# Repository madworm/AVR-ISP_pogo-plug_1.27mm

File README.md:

AVR-ISP_pogo-plug_1.27mm
========================

LAYOUT FILES: AVR-ISP adapter: 6pin (2.54mm) --> 6pin pogo-pins (1.27mm). 

When your boards get smaller and smaller and it gets harder and harder
to find a spot for the programming connector.

Pogo-pin type: "P50 - E2", 0.68mm body diameter, 0.9mm head diameter.

PCB thickness: 0.6mm !

---

Before having PC-boards made, please make sure you know about your manufacturer's peculiarities!
Especially drill-sizes and their tolerances may vary too much and give you trouble.

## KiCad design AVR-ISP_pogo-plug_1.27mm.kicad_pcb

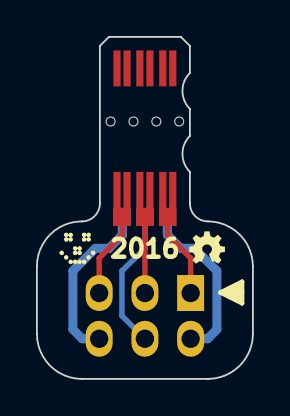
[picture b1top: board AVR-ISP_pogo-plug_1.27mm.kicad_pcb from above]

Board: 2 copper layers, 12.0 x 19.0 mm, 4 parts (0 on the bottom side), 6 nets.

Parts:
G1: LED_smile_silkscreen_2mm
G2: OSHW-logo_silkscreen_2mm
P1: CONN_6; MADW__PIN_ARRAY_3x2_2.54mm
P2: CONN_6; MADW__PIN_ARRAY_3x2_1.27mm

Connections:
/GND: P1.6, P2.6
/MISO: P1.1, P2.1
/MOSI: P1.4, P2.4
/RESET: P1.5, P2.5
/SCK: P1.3, P2.3
/V-target: P1.2, P2.2

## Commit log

2013-05-25 Initial commit.
2013-05-27 Updated 'README.md'.
2013-06-09 Added 2 break-away sub-boards supposed to act as pogo-pin stabilizers.
2013-06-09 Reduced to just one stabilizer board.
2013-06-10 Board outline tweaks.
2013-06-13 Rounded corners.
2013-07-05 Got the boards: marginal annular ring --> increased pad-size to 1.65mm.
2013-09-02 Changed some traces. Don't connect to pads next to drills.
2013-09-04 Added sub-boards to triple board thickness for better pogo-pin alignment.
2013-09-29 Drill-size issues again...
2013-09-29 Stacking PCBs doesn't work. Too imprecise. THICK PCB could solve it.
2013-09-29 Revert "Stacking PCBs doesn't work. Too imprecise. THICK PCB could solve it."
    This reverts commit 490f224e26ced886a5e1a4095987a5f097893897.
2013-09-29 Revert "Drill-size issues again..."
    This reverts commit 78704ad755869ccbc9e371843dd45850562db76e.
2013-09-29 Revert "Added sub-boards to triple board thickness for better pogo-pin alignment."
    This reverts commit 808a31bfee8c9cebc64c52d68362d3861d50fe81.
2013-10-01 New idea how to assemble the pogo-pins.
    * one sub-board is an 'align tool' with small drills,
    so the heads can register with them.
    * the other's holes are large enough for the pins'
    shafts. This should stabilize the pins sideways.
2013-10-10 Experimenting with yet another scheme (0.6mm PCBs).
2013-10-10 Changed the board-outline a bit.
2013-10-10 Made it look more like a key.
2013-10-10 Added 'Docs'.
2013-10-10 Using 'Solder mask win width' polygonizes round pad outlines :-(
2013-10-17 Removed solder mask at board edge <--> pogo-pin flat on pads.
2013-12-11 Added suggested footprint info to Docs folder.
2013-12-19 Tweaked split pads footprint for hopefully better axial alignment.
2013-12-19 Board outline tweaks. Looks more like a key + better pin-1 ident.
2014-05-12 Tweaks.
2014-09-18 Removed "key-hole" to allow for 90° 3x2 header.
2015-07-23 Tweakes pogo footprint. Space for dot of glue.
2015-07-23 Fixed pad offset.
2016-01-26 Shorter pogo-pin split-pad footprints. Less chance to mess things up.
2016-02-02 Added 4 drill hits to allow wiring down pogo-pins for assembly.
2016-04-12 Created a panel. Just for the heck of it.
2016-04-12 Panel with mouse-bites instead of v-scoring.
2016-04-12 Well... routing paths should really be correct.
2016-08-19 Revert "Added 4 drill hits to allow wiring down pogo-pins for assembly."
    This reverts commit c23f7a8ddcae17a2ea3c2f7512045aeab9fe0c27.
    Reason: mechanical stability severely compromised.
2016-08-19 Renamed gerber files to match KiCad's new standard names.
